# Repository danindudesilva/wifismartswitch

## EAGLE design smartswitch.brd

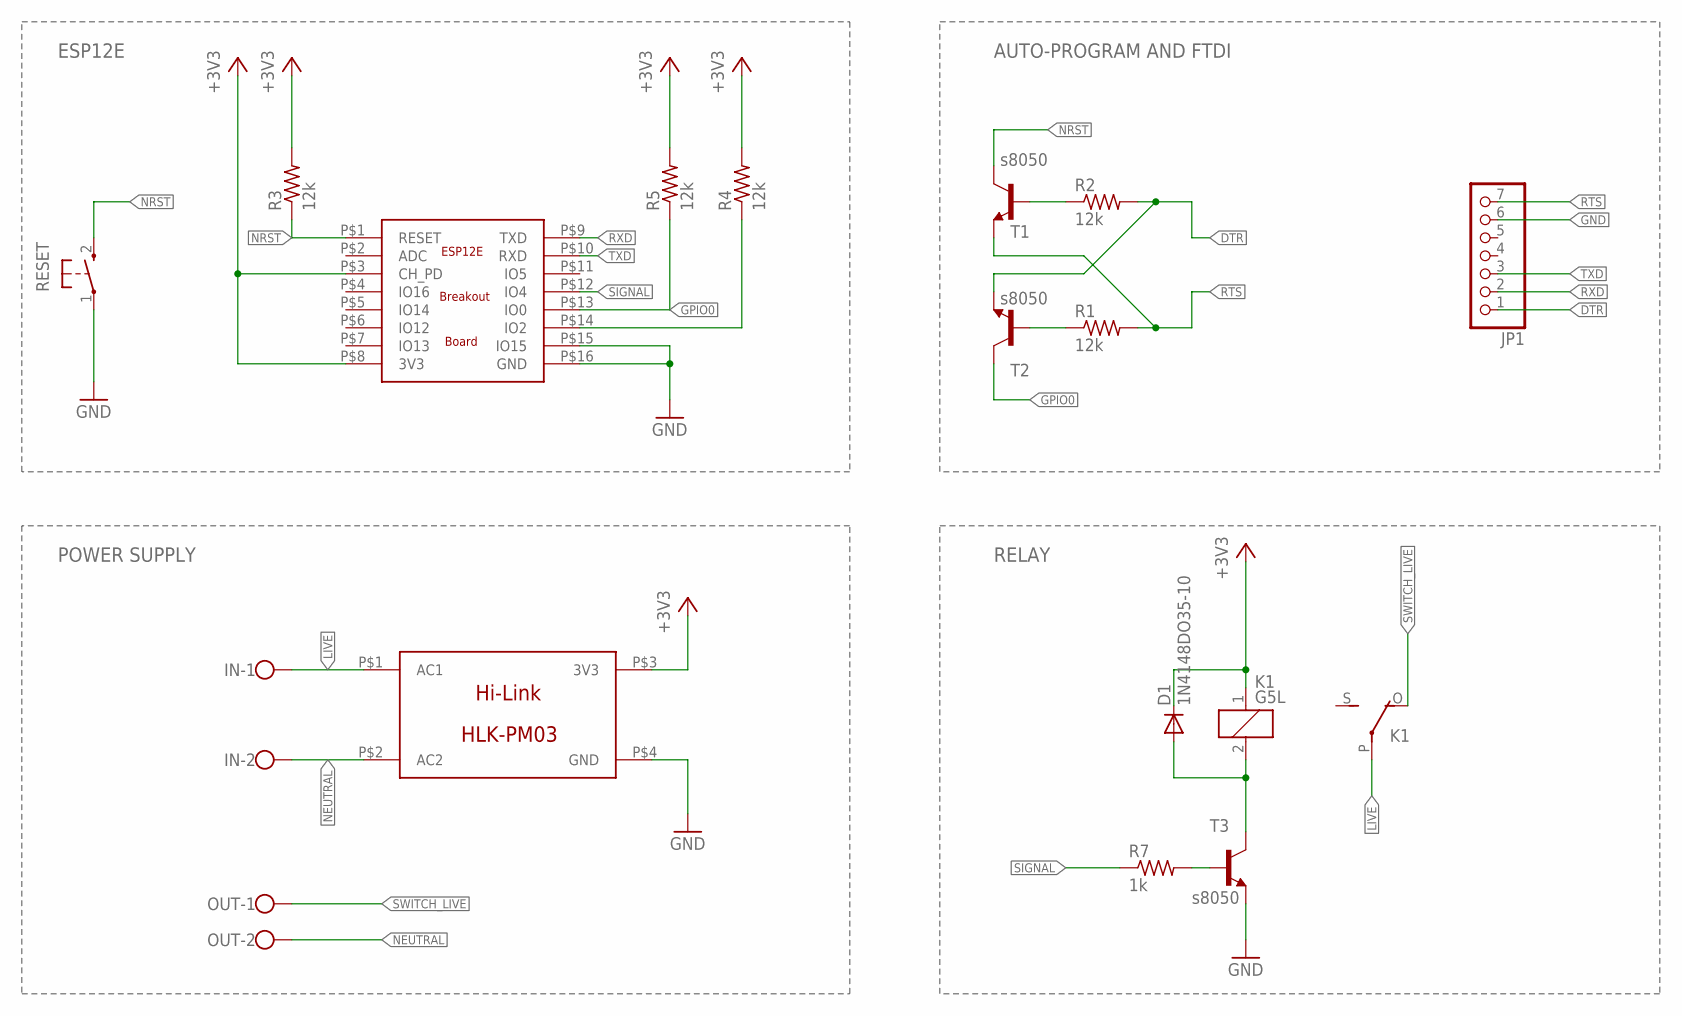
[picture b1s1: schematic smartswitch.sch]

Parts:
D1: 1N4148DO35-10; DO35-10
IN: W237-102
JP1: PINHD-1X7; 1X07
K1: G5L; G5LE
OUT: W237-102
R1, R2, R3, R4, R5: 12k; 0309/12
R7: 1k; 0309/12
RESET: PB; PBTH
T1, T2, T3: s8050; TO92-EBC
U$1: ESP12E_BREAKOUT; ESP12E
U$2: HLK-PM03

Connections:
+3V3: D1.C, K1.1, R3.2, R4.2, R5.2, U$1.P$3 (CH_PD), U$1.P$8 (3V3), U$2.P$3 (3V3)
DTR: JP1.1, R2.2, T2.E
GND: JP1.6, RESET.1, T3.E, U$1.P$15 (IO15), U$1.P$16 (GND), U$2.P$4 (GND)
GPIO0: R5.1, T2.C, U$1.P$13 (IO0)
LIVE: IN.1, K1.P, U$2.P$1 (AC1)
unnamed: R2.1, T1.B
unnamed: R1.1, T2.B
unnamed: R4.1, U$1.P$14 (IO2)
unnamed: D1.A, K1.2, T3.C
unnamed: R7.2, T3.B
NEUTRAL: IN.2, OUT.2, U$2.P$2 (AC2)
NRST: R3.1, RESET.2 (S), T1.C, U$1.P$1 (RESET)
RTS: JP1.7, R1.2, T1.E
RXD: JP1.2, U$1.P$9 (TXD)
SIGNAL: R7.1, U$1.P$12 (IO4)
SWITCH_LIVE: K1.O, OUT.1
TXD: JP1.3, U$1.P$10 (RXD)

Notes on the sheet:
ESP12E
AUTO-PROGRAM AND FTDI
POWER SUPPLY
RELAY

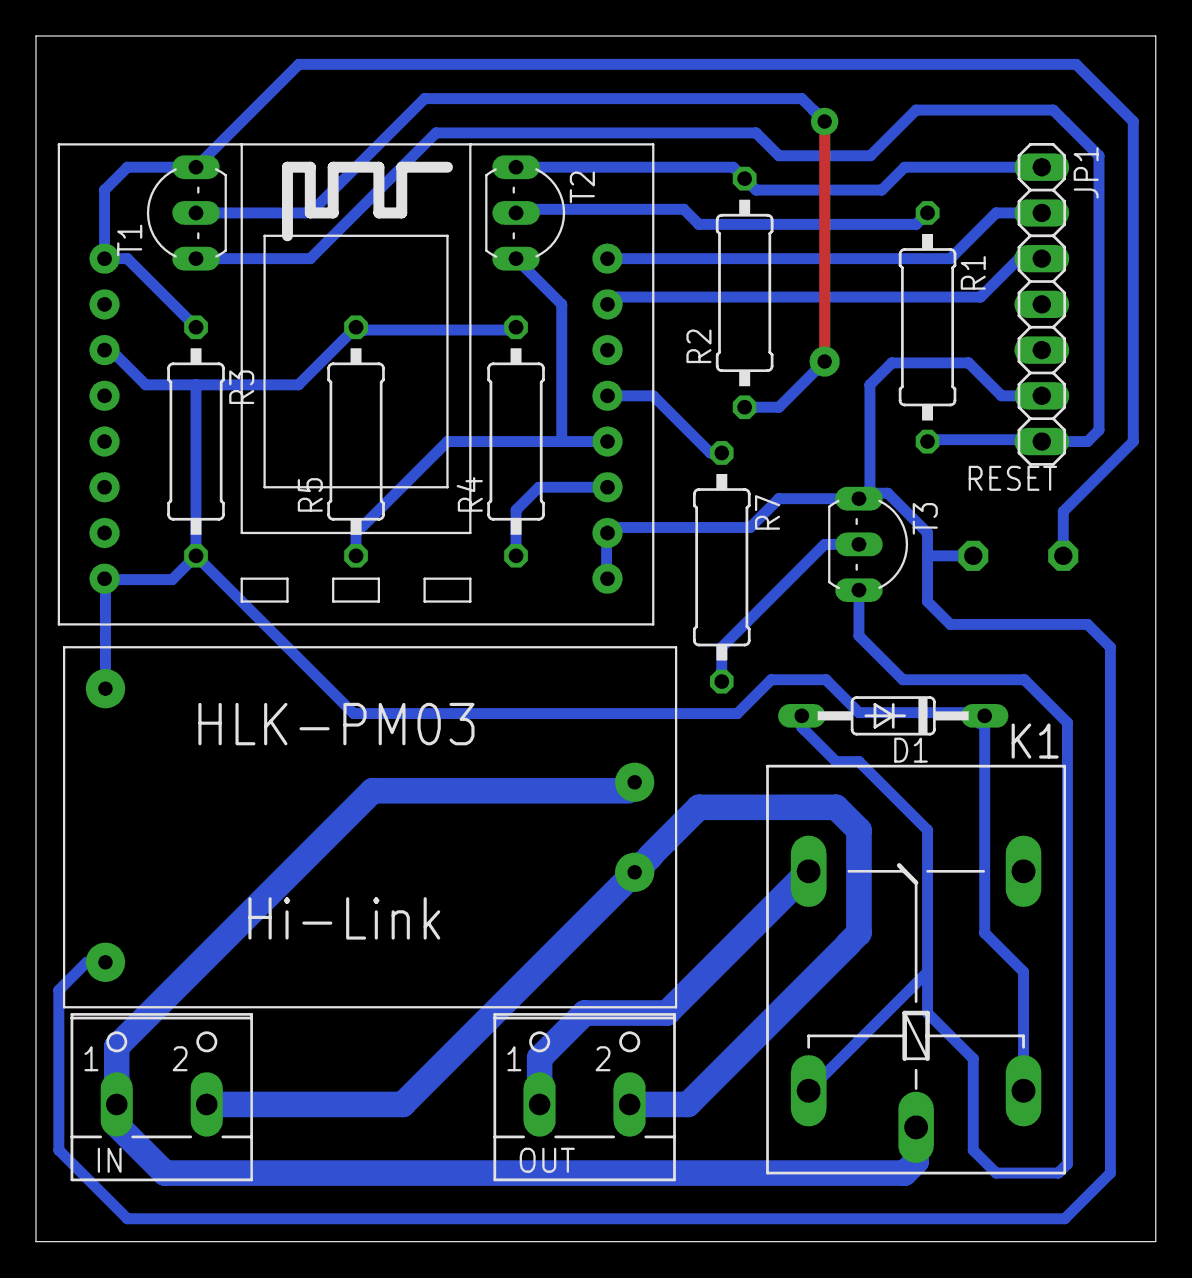
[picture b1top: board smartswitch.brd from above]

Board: 2 copper layers, 62.2 x 67.0 mm, 17 parts (0 on the bottom side), 17 nets.
